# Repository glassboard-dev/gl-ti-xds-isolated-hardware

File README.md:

<p align="center">
  <h1 align="center">Isolated TI XDS Programmer</h1>
  <p align="center">
    Isolated TI & CMSIS-DAP Compatible Debugger/Programmer
  </p>
</p>

<br />
<p align="center">
    
<p/>

## Usage 💻
The programmer supports SWD, JTAG and cJTAG (2-wire JTAG). In addition to the programming interface, a UART connection is available over two unused pins of the 10pin programming header. These UART pins are connected back to the programmer and are available over the USB host connection as a CDC Serial port. This is useful for sending debug messages, logging and other application data from the target. The programmer also has a side fire push button that can be used for reseting the target device, as well as a jumper to supply power to the target. This is not to act as a substitution for target power, but rather a means to power and program the target micro without applying power to the entire target board.

#### CDC Serial Port
To connect the XDS serial lines to your targets UART, please reference the 10pin programming header pinout below. The current design assumes that you are creating your target hardware and have the ability to route your UART pins to the "unused" pins of the programming header.

**```NOTE - The UART switching for TX<->RX and RX<->TX is done for you on the XDS hardware. The target TX pin sould go to pin 9 of the 10pin programming header.```**

## Development ⚡
The Isolated XDS hardware is currently developed in the open source ECAD software [KiCAD](https://www.kicad.org/). The board was created using as many of the included component symbols and footprints as possible.

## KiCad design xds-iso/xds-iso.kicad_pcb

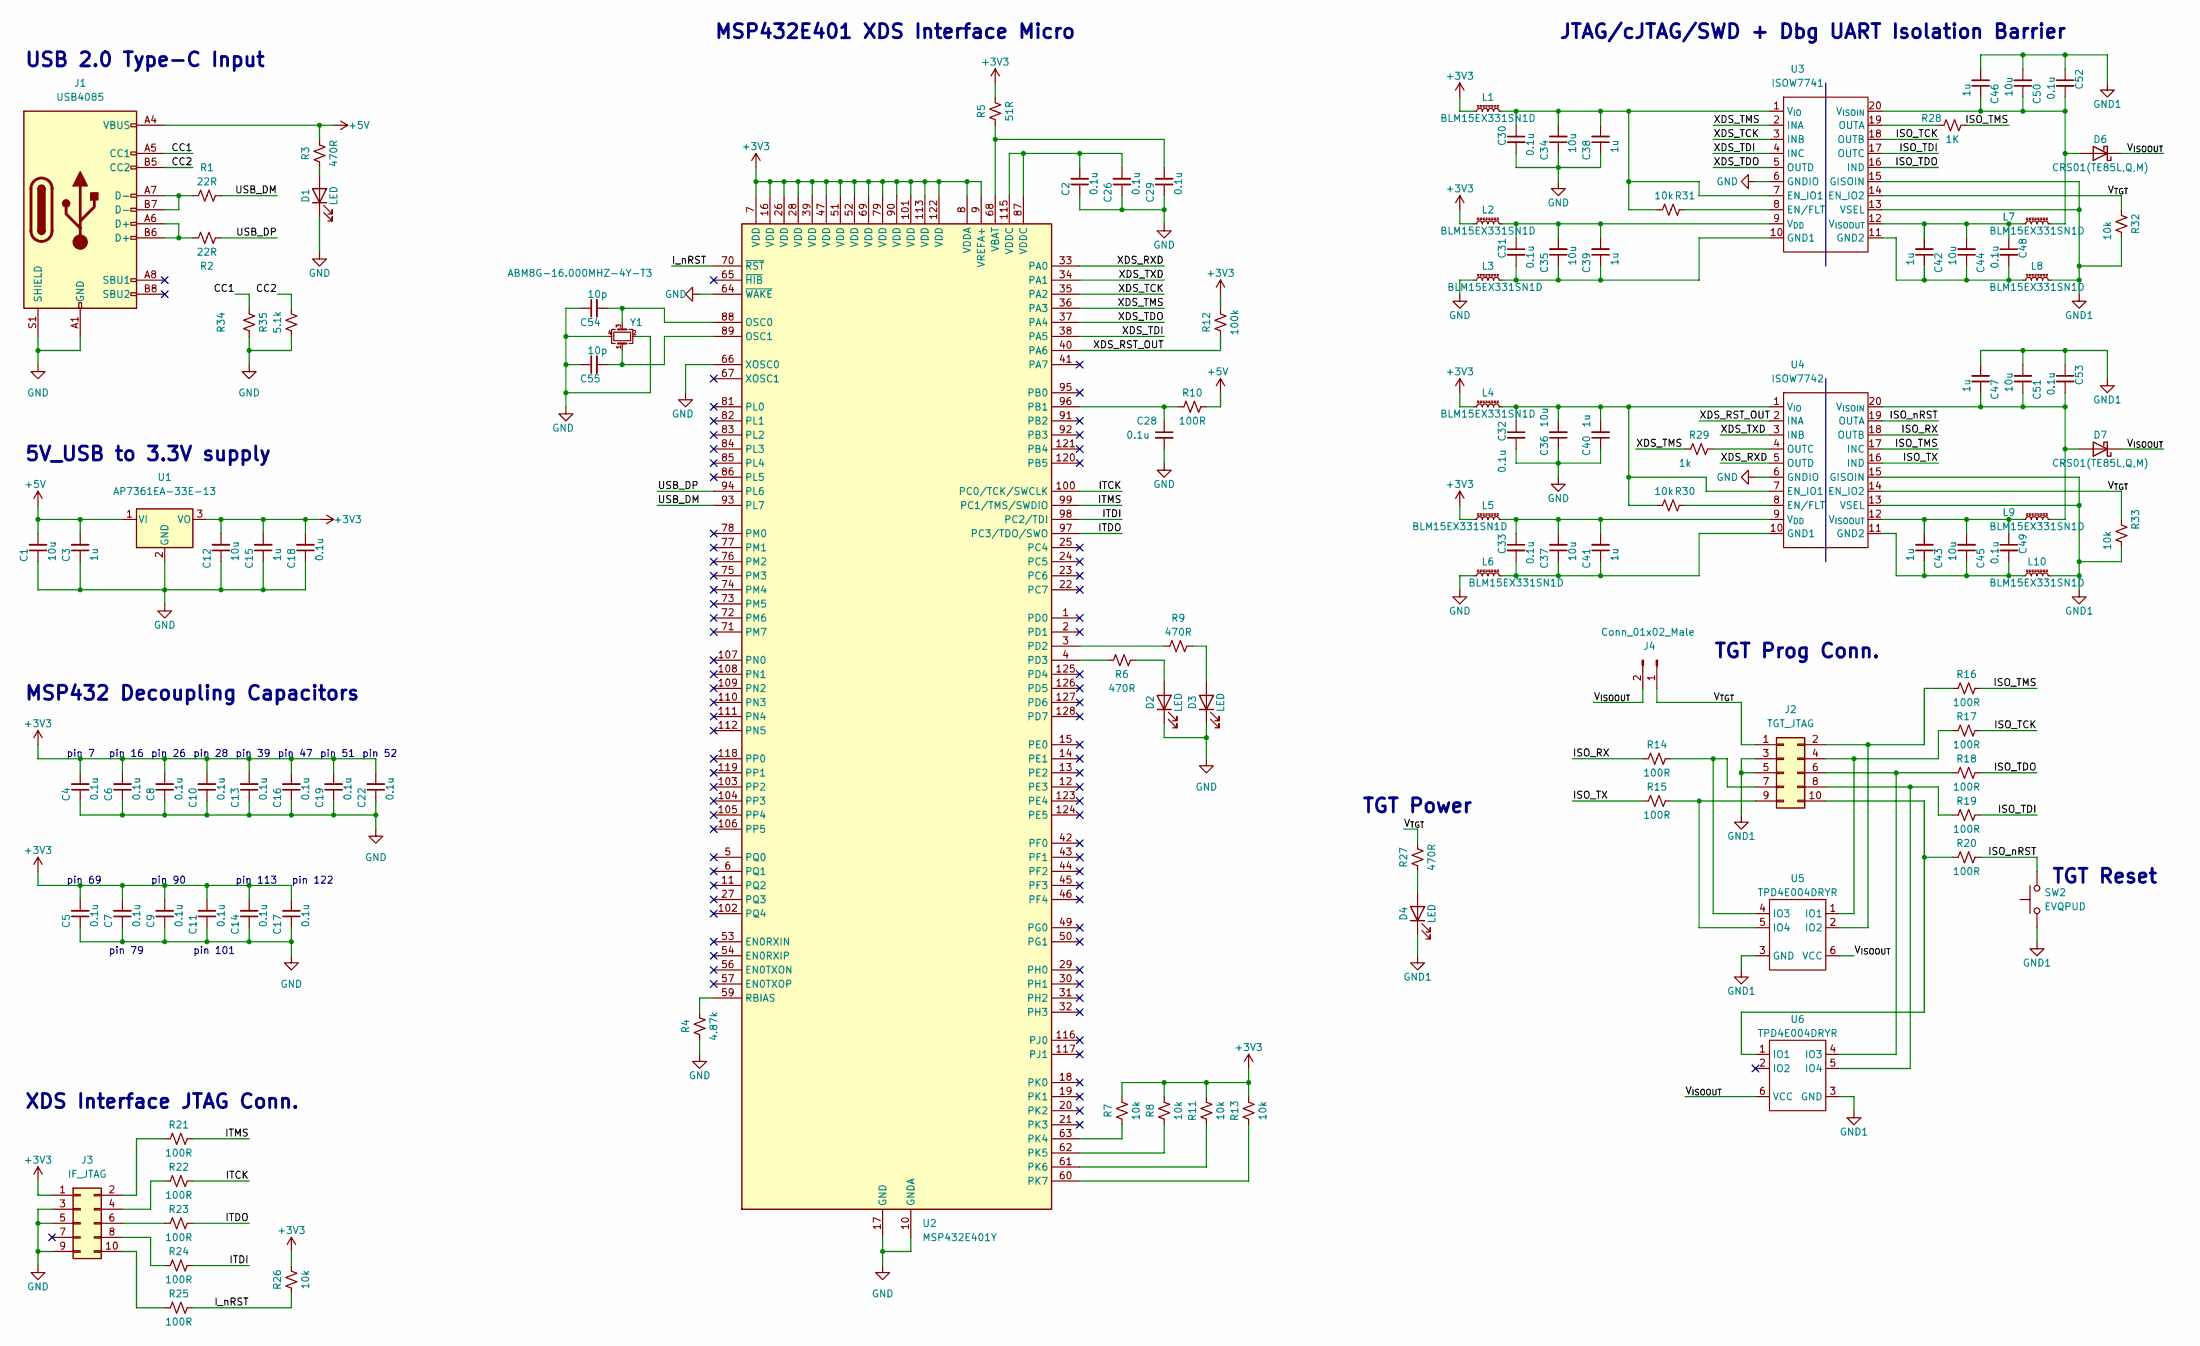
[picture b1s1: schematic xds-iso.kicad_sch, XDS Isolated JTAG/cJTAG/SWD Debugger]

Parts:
C1, C12, C34, C35, C36, C37, C44, C45, C50, C51: 10u; C_0805_2012Metric
C2, C4, C5, C6, C7, C8, C9, C10, C11, C13, C14, C16, C17, C18, C19, C22, C26, C28, C29, C30, C31, C32, C33, C48, C49, C52, C53: 0.1u; C_0402_1005Metric
C3, C15, C38, C39, C40, C41, C42, C43, C46, C47: 1u; C_0603_1608Metric
C54, C55: 10p; C_0402_1005Metric
D1, D2, D3, D4: LED; LED_0603_1608Metric
D6, D7: CRS01(TE85L,Q,M); D_SOD-123F
J1: USB4085; USB_C_Receptacle_GCT_USB4085
J2: TGT_JTAG; PinHeader_2x05_P1.27mm_Vertical_SMD
J3: IF_JTAG; PinHeader_2x05_P1.27mm_Vertical_SMD
J4: Conn_01x02_Male; PinHeader_1x02_P2.54mm_Vertical
L1, L2, L3, L4, L5, L6, L7, L8, L9, L10: BLM15EX331SN1D; L_0402_1005Metric
R1, R2: 22R; R_0402_1005Metric
R3, R6, R9, R27: 470R; R_0402_1005Metric
R4: 4.87k; R_0402_1005Metric
R5: 51R; R_0402_1005Metric
R7, R8, R11, R13, R26, R30, R31, R32, R33: 10k; R_0402_1005Metric
R10, R14, R15, R16, R17, R18, R19, R20, R21, R22, R23, R24, R25: 100R; R_0402_1005Metric
R12: 100k; R_0402_1005Metric
R28: 1K; R_0402_1005Metric
R29: 1k; R_0402_1005Metric
R34: R_0402_1005Metric
R35: 5.1k; R_0402_1005Metric
SW2: EVQPUD; Panasonic_EVQPUM_EVQPUD
U1: AP7361EA-33E-13; SOT-223-3_TabPin2
U2: MSP432E401Y; LQFP-128_14x14mm_P0.4mm
U3: ISOW7741; SOIC-20
U4: ISOW7742; SOIC-20
U5, U6: TPD4E004DRYR; Fairchild_MicroPak-6_1.0x1.45mm_P0.5mm
Y1: ABM8G-16.000MHZ-4Y-T3; Crystal_SMD_Abracon_ABM10-4Pin_2.5x2.0mm

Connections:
+3V3: C4.2, C5.2, C6.2, C7.2, C8.2, C9.2, C10.2, C11.2, C12.2, C13.2, C14.2, C15.2, C16.2, C17.2, C18.2, C19.2, C22.2, J3.1, L1.1, L2.1, L4.1, L5.1, R5.2, R7.2, R8.2, R11.2, R12.2, R13.2, R26.2, U1.3 (VO), U2.7 (VDD), U2.8 (VDDA), U2.9 (VREFA+), U2.16 (VDD), U2.26 (VDD), U2.28 (VDD), U2.39 (VDD), U2.47 (VDD), U2.51 (VDD), U2.52 (VDD), U2.69 (VDD), U2.79 (VDD), U2.90 (VDD), U2.101 (VDD), U2.113 (VDD), U2.122 (VDD)
+5V: C1.2, C3.2, J1.A4 (VBUS), J1.A9 (VBUS), J1.B4 (VBUS), J1.B9 (VBUS), R3.2, R10.2, U1.1 (VI)
/CC1: J1.A5 (CC1), R34.2
/CC2: J1.B5 (CC2), R35.2
/ISO_RX: R14.1, U4.18 (OUTB)
/ISO_TCK: R17.2, U3.18 (OUTB)
/ISO_TDI: R19.2, U3.17 (OUTC)
/ISO_TDO: R18.2, U3.16 (IND)
/ISO_TMS: R16.2, R28.2, U4.17 (INC)
/ISO_TX: R15.1, U4.16 (IND)
/ISO_nRST: R20.2, SW2.2, U4.19 (OUTA)
/ITCK: R22.2, U2.100 (PC0/TCK/SWCLK)
/ITDI: R24.2, U2.98 (PC2/TDI)
/ITDO: R23.2, U2.97 (PC3/TDO/SWO)
/ITMS: R21.2, U2.99 (PC1/TMS/SWDIO)
/I_nRST: R25.2, R26.1, U2.70 (~RST)
/USB_DM: R1.2, U2.93 (PL7)
/USB_DP: R2.1, U2.94 (PL6)
/V_{ISOOUT}: D6.1 (K), D7.1 (K), J4.2, U5.6 (VCC), U6.6 (VCC)
/V_{TGT}: J2.1, J4.1, R27.2, R32.1, R33.1, U3.14 (EN_IO2), U4.14 (EN_IO2)
/XDS_RST_OUT: R12.1, U2.40 (PA6), U4.2 (INA)
/XDS_RXD: U2.33 (PA0), U4.5 (OUTD)
/XDS_TCK: U2.35 (PA2), U3.3 (INB)
/XDS_TDI: U2.38 (PA5), U3.4 (INC)
/XDS_TDO: U2.37 (PA4), U3.5 (OUTD)
/XDS_TMS: R29.1, U2.36 (PA3), U3.2 (INA)
/XDS_TXD: U2.34 (PA1), U4.3 (INB)
GND: C1.1, C2.1, C3.1, C4.1, C5.1, C6.1, C7.1, C8.1, C9.1, C10.1, C11.1, C12.1, C13.1, C14.1, C15.1, C16.1, C17.1, C18.1, C19.1, C22.1, C26.1, C28.2, C29.1, C30.2, C32.2, C34.1, C36.1, C38.1, C40.1, C54.1, C55.1, D1.1 (K), D2.1 (K), D3.1 (K), J1.A1 (GND), J1.A12 (GND), J1.B1 (GND), J1.B12 (GND), J1.S1 (SHIELD), J3.3, J3.5, J3.9, L3.1, L6.1, R4.1, R34.1, R35.1, U1.2 (GND), U2.10 (GNDA), U2.17 (GND), U2.48 (GND), U2.55 (GND), U2.58 (GND), U2.64 (~WAKE), U2.66 (XOSC0), U2.80 (GND), U2.114 (GND), U3.6 (GNDIO), U4.6 (GNDIO), Y1.2, Y1.4
GND1: C46.2, C47.2, C50.2, C51.2, C52.1, C53.1, D4.1 (K), J2.3, J2.5, L8.1, L10.1, R32.2, R33.2, SW2.1, U3.13 (VSEL), U3.15 (GISOIN), U4.13 (VSEL), U4.15 (GISOIN), U5.3 (GND), U6.3 (GND)
unnamed: C2.2, C26.2, U2.87 (VDDC), U2.115 (VDDC)
unnamed: C28.1, R10.1, U2.96 (PB1)
unnamed: C29.2, R5.1, U2.68 (VBAT)
unnamed: C30.1, C34.2, C38.2, L1.2, R31.2, U3.1 (V_{IO}), U3.7 (EN_IO1)
unnamed: C31.1, C35.2, C39.2, L2.2, U3.9 (V_{DD})
unnamed: C31.2, C35.1, C39.1, L3.2, U3.10 (GND1)
unnamed: C32.1, C36.2, C40.2, L4.2, R30.2, U4.1 (V_{IO}), U4.7 (EN_IO1)
unnamed: C33.1, C37.2, C41.2, L5.2, U4.9 (V_{DD})
unnamed: C33.2, C37.1, C41.1, L6.2, U4.10 (GND1)
unnamed: C42.1, C44.1, C48.2, L8.2, U3.11 (GND2)
unnamed: C42.2, C44.2, C48.1, L7.2, U3.12 (V_{ISOOUT})
unnamed: C43.1, C45.1, C49.2, L10.2, U4.11 (GND2)
unnamed: C43.2, C45.2, C49.1, L9.2, U4.12 (V_{ISOOUT})
unnamed: C46.1, C50.1, C52.2, D6.2 (A), L7.1, U3.20 (V_{ISOIN})
unnamed: C47.1, C51.1, C53.2, D7.2 (A), L9.1, U4.20 (V_{ISOIN})
unnamed: C54.2, U2.88 (OSC0), Y1.3
unnamed: C55.2, U2.89 (OSC1), Y1.1
unnamed: D1.2 (A), R3.1
unnamed: D2.2 (A), R6.2
unnamed: D3.2 (A), R9.2
unnamed: D4.2 (A), R27.1
unnamed: J1.A6 (D+), J1.B6 (D+), R2.2
unnamed: J1.A7 (D-), J1.B7 (D-), R1.1
unnamed: J2.2, R16.1, U5.2 (IO2)
unnamed: J2.4, R17.1, U5.1 (IO1)
unnamed: J2.6, R18.1, U6.4 (IO3)
unnamed: J2.7, R14.2, U5.4 (IO3)
unnamed: J2.8, R19.1, U6.5 (IO4)
unnamed: J2.9, R15.2, U5.5 (IO4)
unnamed: J2.10, R20.1, U6.1 (IO1)
unnamed: J3.2, R21.1
unnamed: J3.4, R22.1
unnamed: J3.6, R23.1
unnamed: J3.8, R24.1
unnamed: J3.10, R25.1
unnamed: R4.2, U2.59 (RBIAS)
unnamed: R6.1, U2.4 (PD3)
unnamed: R7.1, U2.63 (PK4)
unnamed: R8.1, U2.62 (PK5)
unnamed: R9.1, U2.3 (PD2)
unnamed: R11.1, U2.61 (PK6)
unnamed: R13.1, U2.60 (PK7)
unnamed: R28.1, U3.19 (OUTA)
unnamed: R29.2, U4.4 (OUTC)
unnamed: R30.1, U4.8 (EN/FLT)
unnamed: R31.1, U3.8 (EN/FLT)

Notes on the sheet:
TGT Reset
pin 113
pin 90
MSP432E401 XDS Interface Micro
pin 16
pin 52
USB 2.0 Type-C Input
JTAG/cJTAG/SWD + Dbg UART Isolation Barrier
TGT Power
MSP432 Decoupling Capacitors
pin 47
pin 51
pin 69
pin 7
pin 101
TGT Prog Conn.
pin 122
XDS Interface JTAG Conn.
pin 26
pin 79
pin 28
pin 39
5V_USB to 3.3V supply

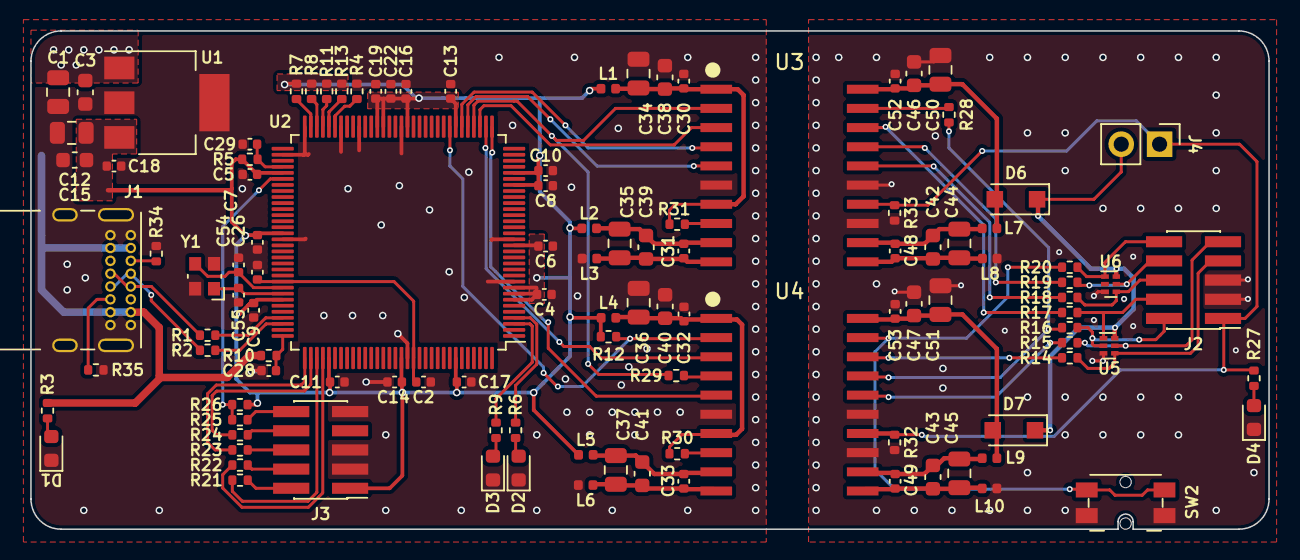
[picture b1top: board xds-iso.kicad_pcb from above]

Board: 2 copper layers, 82.0 x 33.0 mm, 112 parts (0 on the bottom side), 75 nets.

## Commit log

2022-05-21 R01 first commit
2022-05-21 Ignoring the backup folder
2022-05-21 Actually ignore the backups folder
2022-05-23 Remove soldermask between the MSP432 IC pads
2022-06-29 R02 updates supporting cJTAG and SWD
2022-07-13 Changed TMS series resistor to 1k
2022-07-13 Add images and update README
2022-07-13 Update LICENSE
2022-07-13 Final schematic touches
2022-07-14 Added 5.1k pulldowns to the CC1 and CC2 pins to comply with USB Type C spec
2022-07-14 Fix header naming in README

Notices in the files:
README.md:
License: CC BY 4.0
